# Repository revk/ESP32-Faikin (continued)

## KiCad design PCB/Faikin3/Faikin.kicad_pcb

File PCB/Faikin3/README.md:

# PCB

These files are for use in [KiCad](https://www.kicad.org) so can be edited as needed.

You should, technically, remove the A&A and AJK logos as they are trademark. If you are using for yourself, then fine, but you must not trade (i.e. sell boards you make) with these logos.

## Ordering

There are also `production` files for [JLCPCB](https://jlcpcb.com)

When ordering, you need the `gerber.zip`, `bom.csv`, and `position.csv` files.

### PCB

- Different Design: 2
- PCB Thickness: 1.0
- PCB Color: Black

### Assembly

- PCBA Type: Standard
- Assembly Side: Both Sides
- Tooling holes: Added by Customer

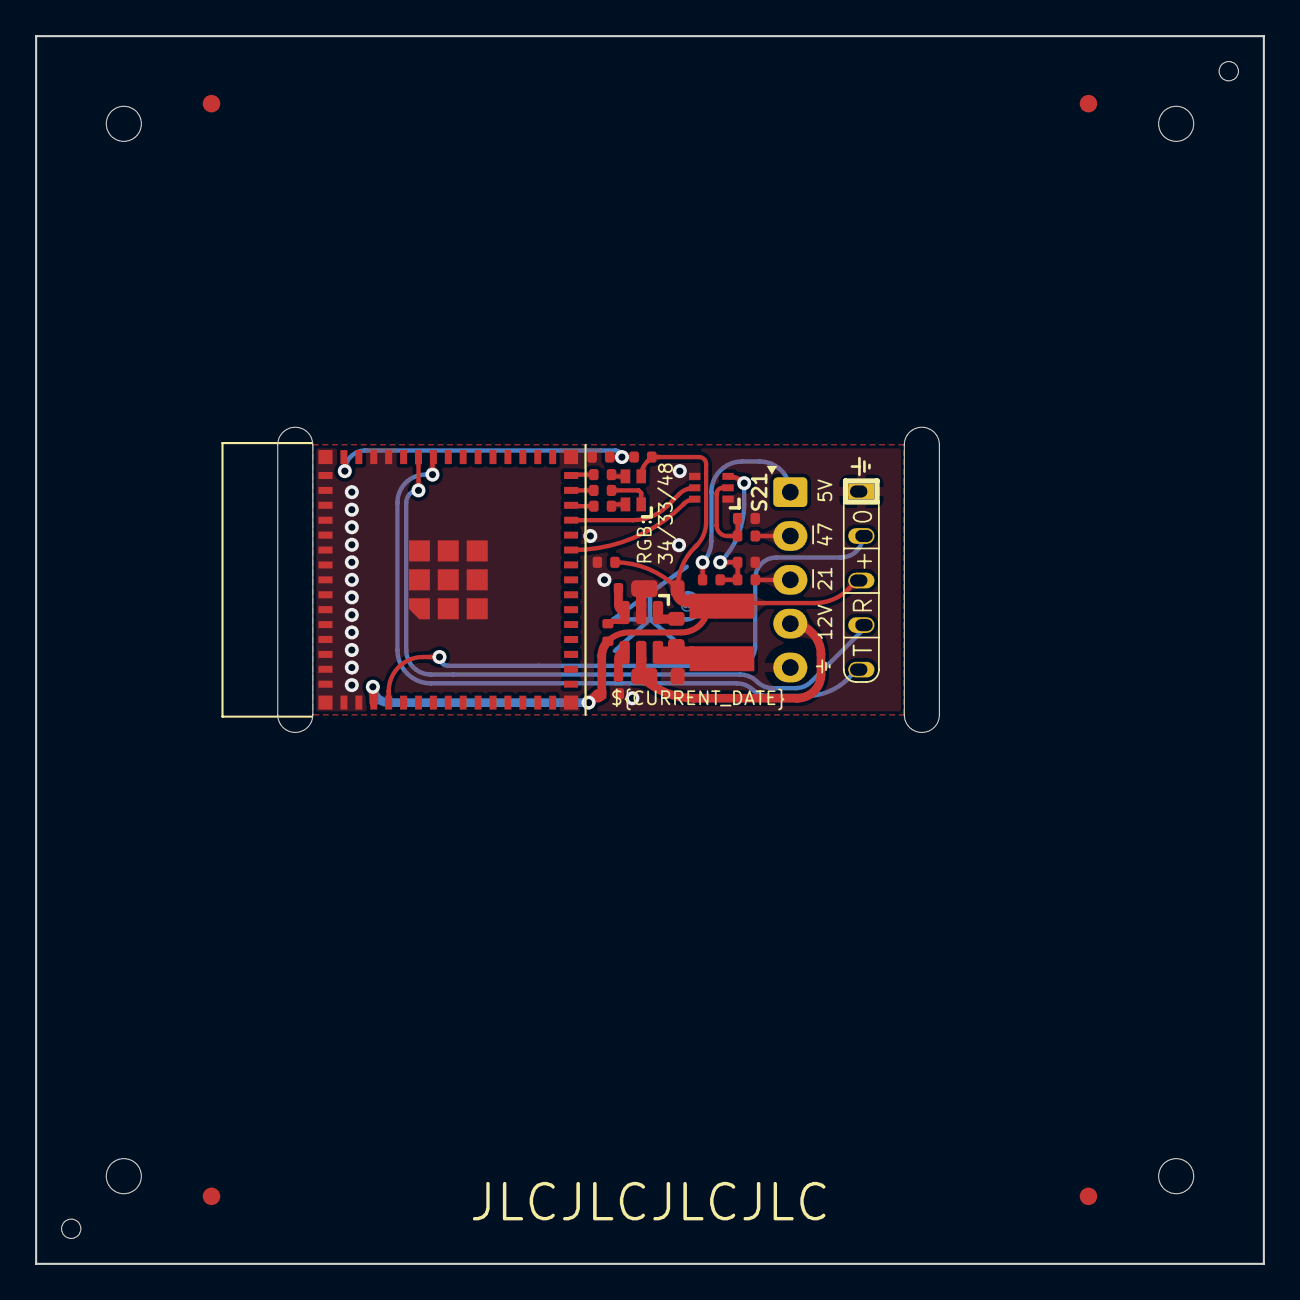
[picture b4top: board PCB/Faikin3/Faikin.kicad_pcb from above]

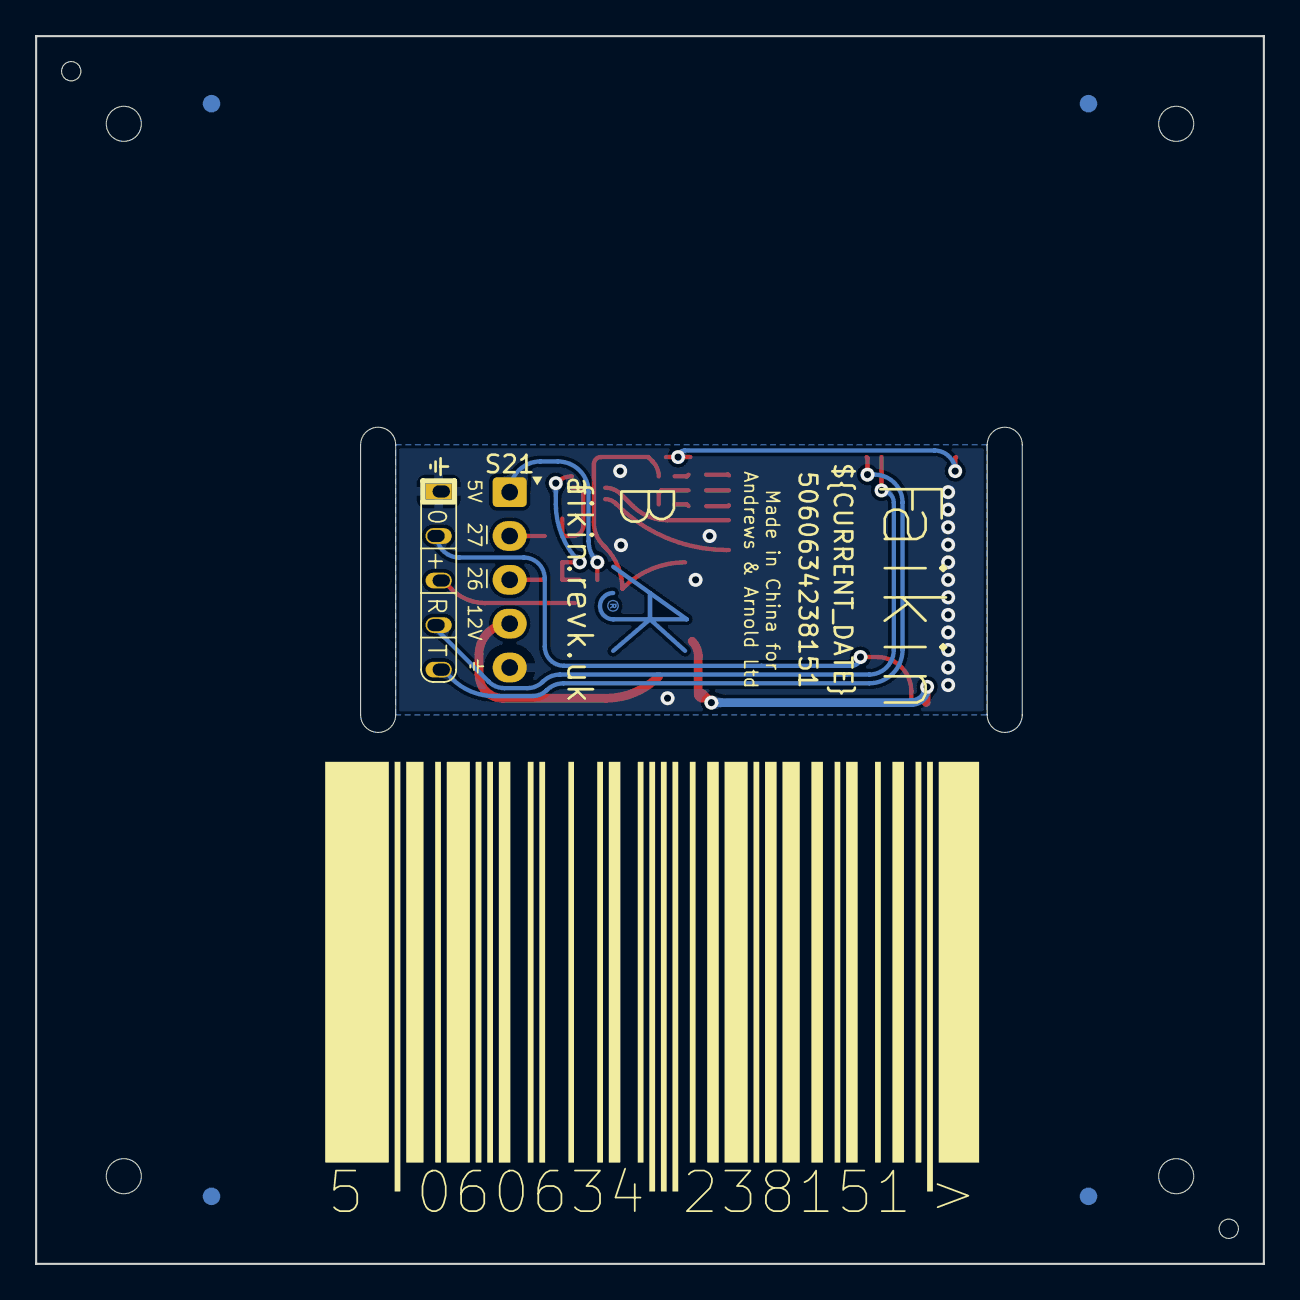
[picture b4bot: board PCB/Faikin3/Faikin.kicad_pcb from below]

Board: 2 copper layers, 70.0 x 70.0 mm, 30 parts (3 on the bottom side), 20 nets.

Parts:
C2: 100nF; C_0402
C3, C4: 33pF; C_0402
C5: 22uF; C_0402
C6: 1uF; C_0402
C8: 10uF 50V; C_0603_
C9: 10uF 6.3V; C_0603_
C10: 100nF; C_0603_
D2: RGB; LED-RGB-1.6x1.6
J1: 1x5; JST_EH_S5B-EH_1x05_P2.50mm_Horizontal
J3: Shelly
L2: 10uH; L_4x4_
Logo1: AJK
PCB1: 70x70; PCB7070
Q1: BSS138PS; SOT-363_SC-70-6
R1: 10k; R_0402
R2, R8: 100R; R_0402
R3: 10K; R_0402
R5: 680R; R_0402
R6: 2K; R_0402
R9: 124k; R_0402_
R10: 39k2; R_0402_
R11: 1M; R_0402_
R12: 220R; R_0402
U2: Barcode; EAN-5060634238151
U3: MD8942; SOT-23-6-MD8942
U4: ESP32-S3-MINI-1
V1, V2: VCUT70

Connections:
+3.3V: C2.1, C5.1, D2.4 (A), J3.3 (3V3), R3.1, U3.8 (VOUT), U4.3 (3V3)
B: R12.2, U4.30 (GPIO48)
DC: J1.4, U3.5 (VIN)
G: R6.2, U4.28 (GPIO33)
GND: C2.2, C3.1, C4.1, C5.2, C6.2, J1.5, J3.1 (GND), Q1.1 (SN), Q1.4 (DP), U3.2 (GND), U3.7 (GND), U4.1 (GND), U4.2 (GND), U4.42 (GND), U4.43 (GND), U4.46 (GND), U4.47 (GND), U4.48 (GND), U4.49 (GND), U4.50 (GND), U4.51 (GND), U4.52 (GND), U4.53 (GND), U4.54 (GND), U4.55 (GND), U4.56 (GND), U4.57 (GND), U4.58 (GND), U4.59 (GND), U4.60 (GND), U4.61 (GND), U4.62 (GND), U4.63 (GND), U4.64 (GND), U4.65 (GND)
unnamed: D2.3 (BK), R12.1
unnamed: D2.2 (GK), R6.1
unnamed: D2.1 (RK), R5.1
unnamed: J1.1, R1.1
unnamed: J1.2, R8.2
unnamed: J1.3, R2.2
unnamed: J3.2 (0), U4.4 (GPIO0)
unnamed: J3.4 (Rx), U4.40 (GPIO44)
unnamed: J3.5 (Tx), U4.39 (GPIO43)
unnamed: C4.2, Q1.2 (GN), R8.1
unnamed: C3.2, Q1.3 (SP), R1.2, R2.1
unnamed: C6.1, R3.2, U4.45 (EN)
R: R5.2, U4.29 (GPIO34)
RX: Q1.6 (DN), U4.25 (GPIO21)
TX: Q1.5 (GP), U4.27 (GPIO47)

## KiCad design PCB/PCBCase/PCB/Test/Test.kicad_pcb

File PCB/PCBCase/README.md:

* PCB Case

This is designed to take an KICad 6 kicad_pcb file and produce an openscad file that is the case.
The problem is that you need 3D models for your parts for this to work sensibly, so the C code has a list of footprints as basic openscad outlines. This is not like the 3D models in KiCad which are accurate, it is simply boxes and shapes that allow for the 3D box to have a sensibly sized cut out for the part.
In many cases this means the model is just a cuboid. But in some cases it is slightly more important as it has the attached connector included.
Any parts of the design that would breach the case cause cut outs and supports in the case surround.

## models

Modules are individual scad instructions, and can be named as the first match of :-

- The footprint name (without `prefix:`)
- The footprint name (without `prefix:`) where single numeric component is replaced with `0`
- The 3D model name(s) in the footprint

The module is called with `pushed` and `hulled` which are Boolean, and in the case of the `0` version, with `n` which is the number that was replaced with 0.

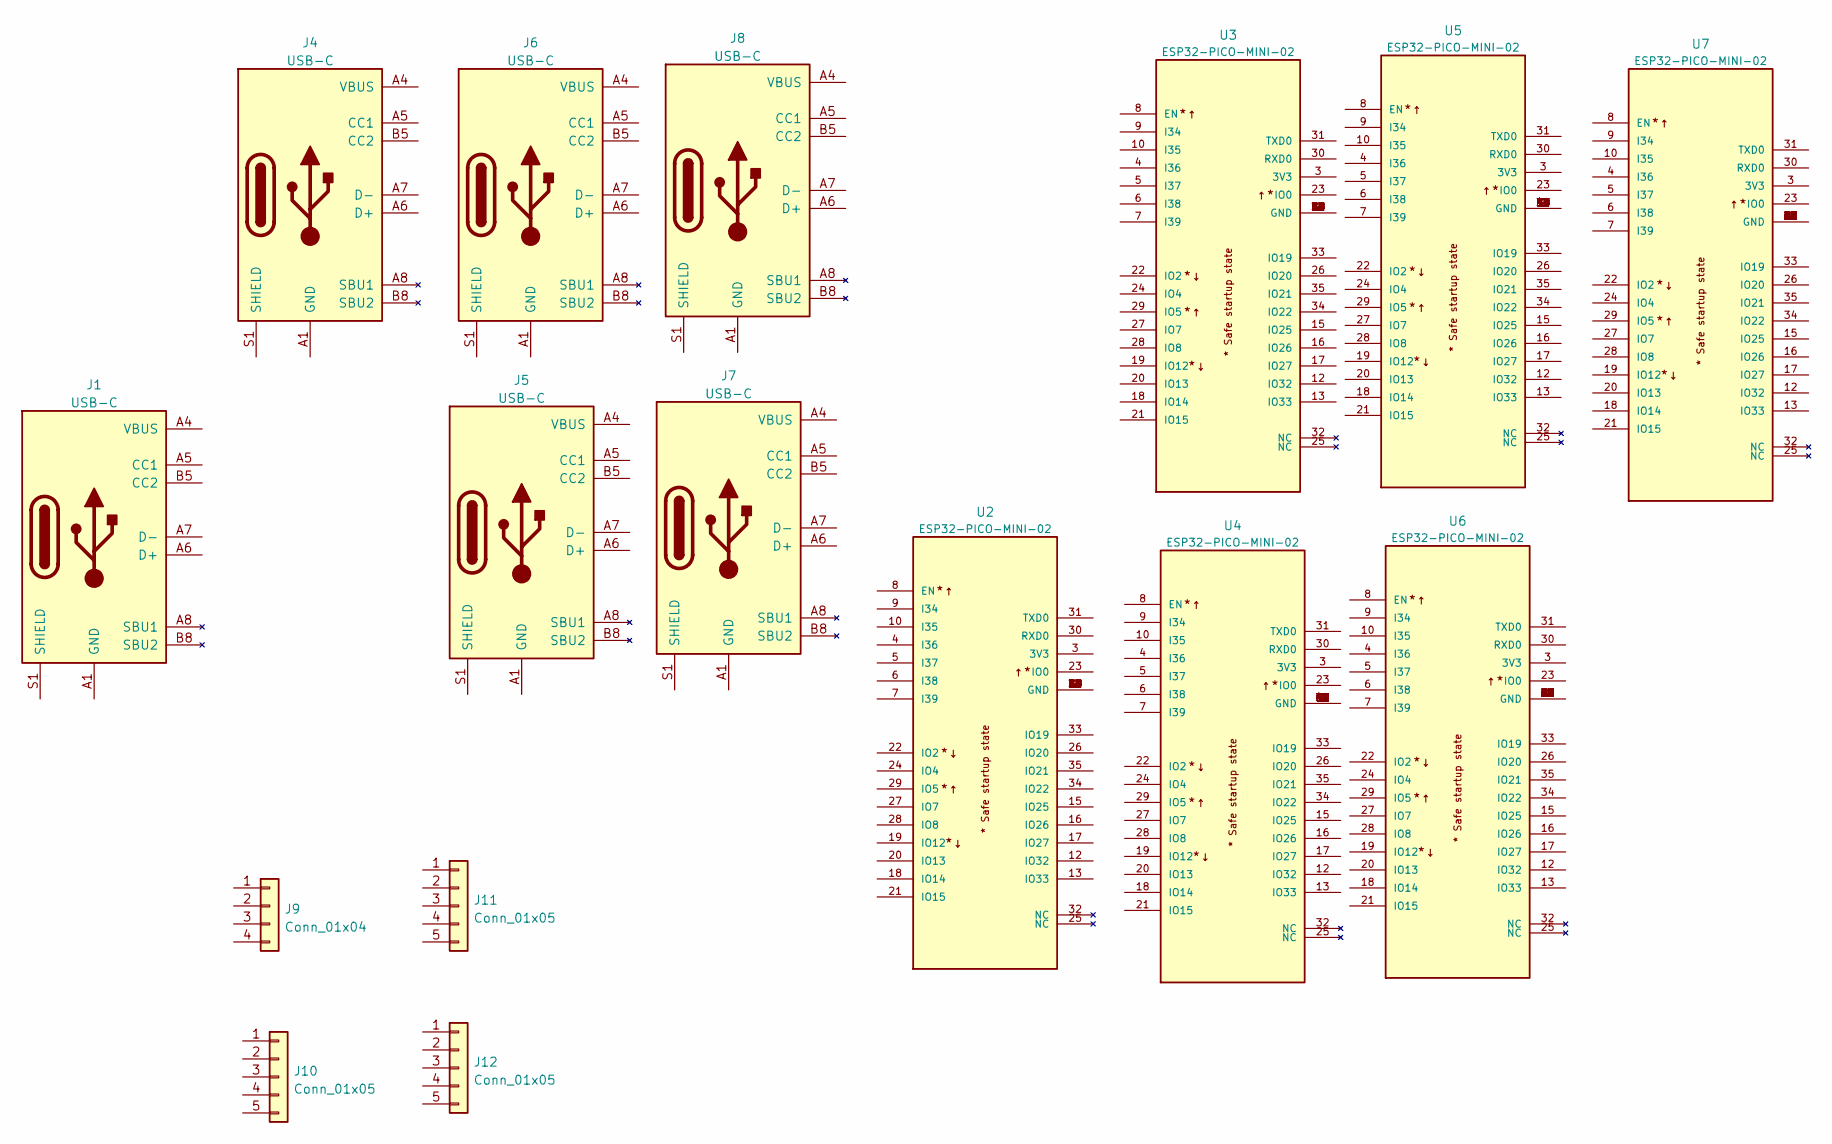
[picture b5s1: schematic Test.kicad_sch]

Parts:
J1, J4, J5, J6, J7, J8: USB-C; USC16-TR-Round
J9: Conn_01x04; JLC-PinHeader_1x04_P2.54mm_Right
J10: Conn_01x05; PTSM-HH-5-RA-P
J11: Conn_01x05; PTSM-HH-5-RA
J12: Conn_01x05; PTSM-HH-5-RA-P-SMD
U2, U3, U4, U5, U6, U7: ESP32-PICO-MINI-02; PARTREV v1.0

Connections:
unnamed: J1.A1 (GND), J1.A12 (GND), J1.B1 (GND), J1.B12 (GND)
unnamed: J1.A4 (VBUS), J1.A9 (VBUS), J1.B4 (VBUS), J1.B9 (VBUS)
unnamed: J1.A6 (D+), J1.B6 (D+)
unnamed: J1.A7 (D-), J1.B7 (D-)
unnamed: J4.A1 (GND), J4.A12 (GND), J4.B1 (GND), J4.B12 (GND)
unnamed: J4.A4 (VBUS), J4.A9 (VBUS), J4.B4 (VBUS), J4.B9 (VBUS)
unnamed: J4.A6 (D+), J4.B6 (D+)
unnamed: J4.A7 (D-), J4.B7 (D-)
unnamed: J5.A1 (GND), J5.A12 (GND), J5.B1 (GND), J5.B12 (GND)
unnamed: J5.A4 (VBUS), J5.A9 (VBUS), J5.B4 (VBUS), J5.B9 (VBUS)
unnamed: J5.A6 (D+), J5.B6 (D+)
unnamed: J5.A7 (D-), J5.B7 (D-)
unnamed: J6.A1 (GND), J6.A12 (GND), J6.B1 (GND), J6.B12 (GND)
unnamed: J6.A4 (VBUS), J6.A9 (VBUS), J6.B4 (VBUS), J6.B9 (VBUS)
unnamed: J6.A6 (D+), J6.B6 (D+)
unnamed: J6.A7 (D-), J6.B7 (D-)
unnamed: J7.A1 (GND), J7.A12 (GND), J7.B1 (GND), J7.B12 (GND)
unnamed: J7.A4 (VBUS), J7.A9 (VBUS), J7.B4 (VBUS), J7.B9 (VBUS)
unnamed: J7.A6 (D+), J7.B6 (D+)
unnamed: J7.A7 (D-), J7.B7 (D-)
unnamed: J8.A1 (GND), J8.A12 (GND), J8.B1 (GND), J8.B12 (GND)
unnamed: J8.A4 (VBUS), J8.A9 (VBUS), J8.B4 (VBUS), J8.B9 (VBUS)
unnamed: J8.A6 (D+), J8.B6 (D+)
unnamed: J8.A7 (D-), J8.B7 (D-)
unnamed: U2.1 (GND), U2.2 (GND), U2.11 (GND), U2.14 (GND), U2.36 (GND), U2.37 (GND), U2.38 (GND), U2.39 (GND), U2.40 (GND), U2.41 (GND), U2.42 (GND), U2.43 (GND), U2.44 (GND), U2.45 (GND), U2.46 (GND), U2.47 (GND), U2.48 (GND), U2.49 (GND), U2.50 (GND), U2.51 (GND), U2.52 (GND), U2.53 (GND)
unnamed: U3.1 (GND), U3.2 (GND), U3.11 (GND), U3.14 (GND), U3.36 (GND), U3.37 (GND), U3.38 (GND), U3.39 (GND), U3.40 (GND), U3.41 (GND), U3.42 (GND), U3.43 (GND), U3.44 (GND), U3.45 (GND), U3.46 (GND), U3.47 (GND), U3.48 (GND), U3.49 (GND), U3.50 (GND), U3.51 (GND), U3.52 (GND), U3.53 (GND)
unnamed: U4.1 (GND), U4.2 (GND), U4.11 (GND), U4.14 (GND), U4.36 (GND), U4.37 (GND), U4.38 (GND), U4.39 (GND), U4.40 (GND), U4.41 (GND), U4.42 (GND), U4.43 (GND), U4.44 (GND), U4.45 (GND), U4.46 (GND), U4.47 (GND), U4.48 (GND), U4.49 (GND), U4.50 (GND), U4.51 (GND), U4.52 (GND), U4.53 (GND)
unnamed: U5.1 (GND), U5.2 (GND), U5.11 (GND), U5.14 (GND), U5.36 (GND), U5.37 (GND), U5.38 (GND), U5.39 (GND), U5.40 (GND), U5.41 (GND), U5.42 (GND), U5.43 (GND), U5.44 (GND), U5.45 (GND), U5.46 (GND), U5.47 (GND), U5.48 (GND), U5.49 (GND), U5.50 (GND), U5.51 (GND), U5.52 (GND), U5.53 (GND)
unnamed: U6.1 (GND), U6.2 (GND), U6.11 (GND), U6.14 (GND), U6.36 (GND), U6.37 (GND), U6.38 (GND), U6.39 (GND), U6.40 (GND), U6.41 (GND), U6.42 (GND), U6.43 (GND), U6.44 (GND), U6.45 (GND), U6.46 (GND), U6.47 (GND), U6.48 (GND), U6.49 (GND), U6.50 (GND), U6.51 (GND), U6.52 (GND), U6.53 (GND)
unnamed: U7.1 (GND), U7.2 (GND), U7.11 (GND), U7.14 (GND), U7.36 (GND), U7.37 (GND), U7.38 (GND), U7.39 (GND), U7.40 (GND), U7.41 (GND), U7.42 (GND), U7.43 (GND), U7.44 (GND), U7.45 (GND), U7.46 (GND), U7.47 (GND), U7.48 (GND), U7.49 (GND), U7.50 (GND), U7.51 (GND), U7.52 (GND), U7.53 (GND)

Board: 2 copper layers, 16 parts (6 on the bottom side), 30 nets, no tracks yet.

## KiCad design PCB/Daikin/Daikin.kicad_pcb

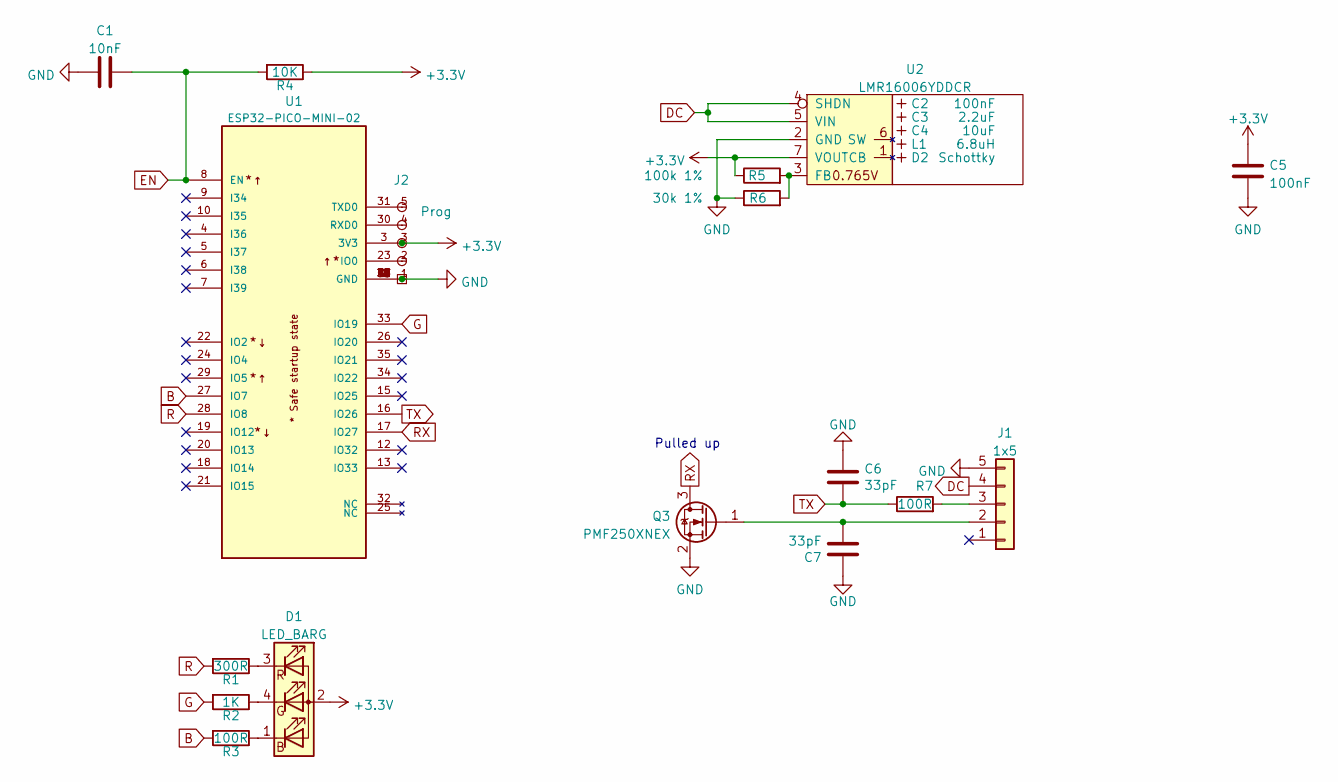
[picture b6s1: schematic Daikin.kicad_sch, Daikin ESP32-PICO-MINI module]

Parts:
C1: 10nF; C_0603; Part No 0603-10nF-50V
C2: 100nF; C_0603_; LCSC Part # C30926
C3: 2.2uF; C_0805_; LCSC Part # C19110
C4: 10uF; C_0805_; LCSC Part # C17024
C5: 100nF; C_0603; Part No 0603-100nF-25V
C6, C7: 33pF; C_0603; Part No 0603-33pF-50V
D1: LED_BARG; MHS190RGBCT; LCSC Part # C409798
D2: Schottky; D_1206_; LCSC Part # C143805
J1: 1x5; JST_EH_S5B-EH_1x05_P2.50mm_Horizontal; LCSC Part # C225427
J2: Prog; Shelly
L1: 6.8uH; L_4x4_; LCSC Part # C354575
Q3: PMF250XNEX; SOT-323_SC-70; Part No PMF250XNEX; LCSC Part # C504047
R1: 300R; R_0603; Part No 0603-680R
R2: 1K; R_0603; Part No 0603-2K
R3: 100R; R_0603; Part No 0603-220R
R4: 10K; R_0603; Part No 0603-10K
R5: 100k 1%; R_0603; LCSC Part # C14675
R6: 30k 1%; R_0603; LCSC Part # C100001
R7: 100R; R_0603; LCSC Part # C105588
U1: ESP32-PICO-MINI-02; PARTREV v1.0; LCSC Part # C2980306
U2: LMR16006YDDCR; SOT-23-Thin-6-Reg; Part No LMR16006YDDCR; LCSC Part # C290195

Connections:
+3.3V: C5.1, D1.2 (A), J2.3 (3V3), R4.1, R5.1, U1.3 (3V3), U2.7 (VOUT)
B: R3.2, U1.27 (IO7)
DC: J1.4, U2.4 (SHDN), U2.5 (VIN)
EN: C1.2, R4.2, U1.8 (EN)
G: R2.2, U1.33 (IO19)
GND: C1.1, C5.2, C6.1, C7.1, J1.5, J2.1 (GND), Q3.2 (S), R6.1, U1.1 (GND), U1.2 (GND), U1.11 (GND), U1.14 (GND), U1.36 (GND), U1.37 (GND), U1.38 (GND), U1.39 (GND), U1.40 (GND), U1.41 (GND), U1.42 (GND), U1.43 (GND), U1.44 (GND), U1.45 (GND), U1.46 (GND), U1.47 (GND), U1.48 (GND), U1.49 (GND), U1.50 (GND), U1.51 (GND), U1.52 (GND), U1.53 (GND), U2.2 (GND)
unnamed: C7.2, J1.2, Q3.1 (G)
unnamed: D1.1 (BK), R3.1
unnamed: D1.3 (RK), R1.1
unnamed: D1.4 (GK), R2.1
unnamed: J1.3, R7.2
unnamed: J2.2 (0), U1.23 (IO0)
unnamed: J2.4 (Rx), U1.30 (RXD0)
unnamed: J2.5 (Tx), U1.31 (TXD0)
unnamed: R5.2, R6.2, U2.3 (FB)
R: R1.2, U1.28 (IO8)
RX: Q3.3 (D), U1.17 (IO27)
TX: C6.2, R7.1, U1.16 (IO26)

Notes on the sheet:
Pulled up

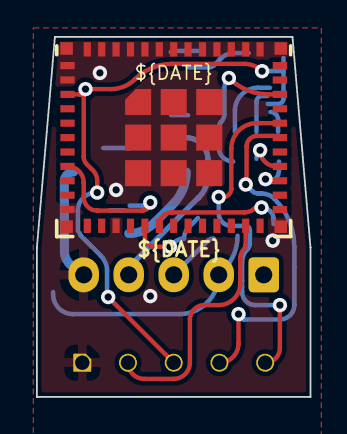
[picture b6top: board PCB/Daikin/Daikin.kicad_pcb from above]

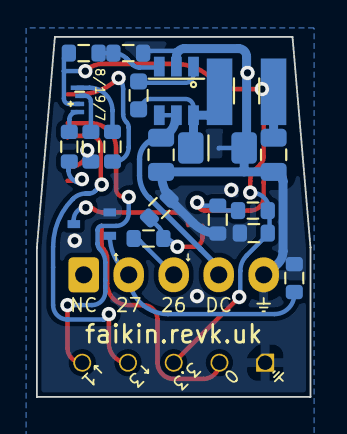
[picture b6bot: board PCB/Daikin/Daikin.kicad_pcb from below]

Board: 2 copper layers, 15.2 x 20.0 mm, 22 parts (20 on the bottom side), 18 nets.

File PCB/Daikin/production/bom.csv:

Designator,Footprint,Quantity,Value,LCSC Part #
C1,C_0603,1,10nF,
C2,C_0603_,1,100nF,C30926
C3,C_0805_,1,2.2uF,C19110
C4,C_0805_,1,10uF,C17024
C5,C_0603,1,100nF,
"C6, C7",C_0603,2,33pF,
D1,MHS190RGBCT,1,LED_BARG,C409798
D2,D_1206_,1,Schottky,C143805
J1,PinHeader_1x05_P2.54mm_Right,1,1x5,C225491
L1,L_4x4_,1,6.8uH,C354575
Q3,SOT-323_SC-70,1,PMF250XNEX,C504047
R1,R_0603,1,300R,
R2,R_0603,1,1K,
"R3, R7",R_0603,2,100R,
R4,R_0603,1,10K,
R5,R_0603,1,100k 1%,C14675
R6,R_0603,1,30k 1%,C100001
U1,ESP32-PICO-MINI-02,1,ESP32-PICO-MINI-02,C2980306
U2,SOT-23-Thin-6-Reg,1,LMR16006YDDCR,C290195

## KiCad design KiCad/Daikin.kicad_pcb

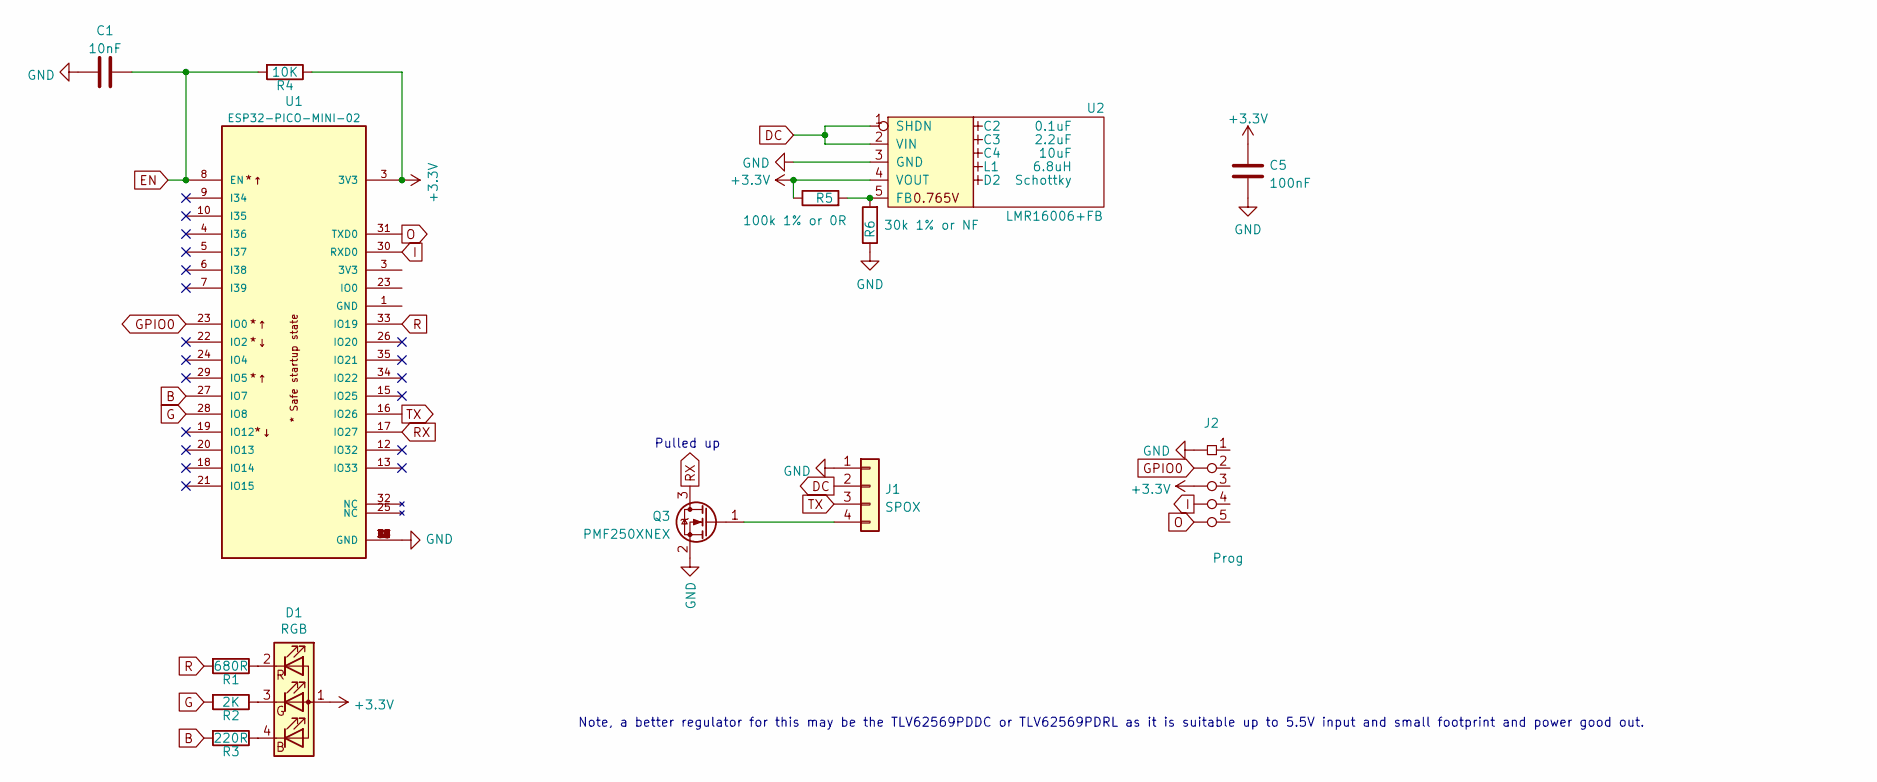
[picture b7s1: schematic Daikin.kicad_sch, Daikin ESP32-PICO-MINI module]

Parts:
C1: 10nF; C_0603; Part No 0603-10nF-50V
C2: 0.1uF; C_0603_; Part No 0603-100nF-50V
C3: 2.2uF; C_0805_; Part No 0805-2.2uF-25V
C4: 10uF; C_0805_; Part No 0805-10uF-16V
C5: 100nF; C_0603; Part No 0603-100nF-25V
D1: RGB; LED-RGB-1.6x1.6; Part No APTF1616LSEEZGKQBKC
D2: Schottky; D_1206_; Part No CD1206-B2100
J1: SPOX; Molex_MiniSPOX_H4RA; Part No 22057025
J2: Prog; Shelly
L1: 6.8uH; L_4x4_; Part No TYA40206R8M-10
Q3: PMF250XNEX; SOT-323_SC-70; Part No PMF250XNEX
R1: 680R; R_0603; Part No 0603-680R
R2: 2K; R_0603; Part No 0603-2K
R3: 220R; R_0603; Part No 0603-220R
R4: 10K; R_0603; Part No 0603-10K
R5: 100k 1% or 0R; R_0603; Part No 0603-100k
R6: 30k 1% or NF; R_0603; Part No 0603-30k
U1: ESP32-PICO-MINI-02; PARTREV v1.0
U2: LMR16006+FB; SOT-23-Thin-6-Reg; Part No LMR16006YQ3

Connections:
+3V3: C5.1, D1.1 (A), J2.3 (3V3), R4.1, R5.1, U1.3 (3V3), U2.4 (VOUT)
B: R3.2, U1.27 (IO7)
DC: J1.2, U2.1 (SHDN), U2.2 (VIN)
EN: C1.2, R4.2, U1.8 (EN)
G: R2.2, U1.28 (IO8)
GND: C1.1, C5.2, J1.1, J2.1 (GND), Q3.2 (S), R6.1, U1.1 (GND), U1.2 (GND), U1.11 (GND), U1.14 (GND), U1.36 (GND), U1.37 (GND), U1.38 (GND), U1.39 (GND), U1.40 (GND), U1.41 (GND), U1.42 (GND), U1.43 (GND), U1.44 (GND), U1.45 (GND), U1.46 (GND), U1.47 (GND), U1.48 (GND), U1.49 (GND), U1.50 (GND), U1.51 (GND), U1.52 (GND), U1.53 (GND), U2.3 (GND)
GPIO0: J2.2 (0), U1.23 (IO0)
I: J2.4 (Rx), U1.30 (RXD0)
unnamed: D1.2 (RK), R1.1
unnamed: D1.3 (GK), R2.1
unnamed: D1.4 (BK), R3.1
unnamed: J1.4, Q3.1 (G)
unnamed: R5.2, R6.2, U2.5 (FB)
O: J2.5 (Tx), U1.31 (TXD0)
R: R1.2, U1.33 (IO19)
RX: Q3.3 (D), U1.17 (IO27)
TX: J1.3, U1.16 (IO26)

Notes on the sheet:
Pulled up
Note, a better regulator for this may be the TLV62569PDDC or TLV62569PDRL as it is suitable up to 5.5V input and small footprint and power good out.

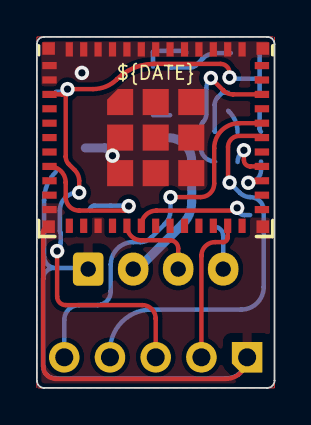
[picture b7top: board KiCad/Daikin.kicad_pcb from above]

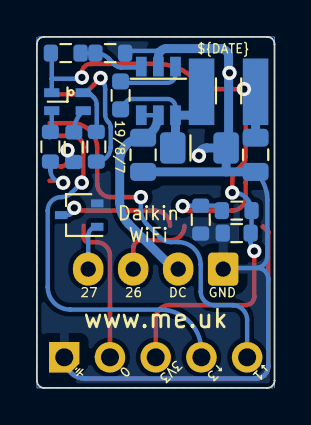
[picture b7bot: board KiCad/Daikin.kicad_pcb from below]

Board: 2 copper layers, 13.2 x 19.5 mm, 19 parts (17 on the bottom side), 17 nets.

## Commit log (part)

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2025-04-14 Beta
2025-04-19 Library update
2025-04-30 Started on Faikin remote
2025-04-30 Tidy
2025-05-01 Faikin remore work
2025-05-03 Faikin power control fixes
2025-05-03 Flag bad mode
2025-05-04 Tweak
2025-05-05 Release
2025-05-09 Handle swing V with no swing H, and change name from `noswingw` to `noswingv`, what was it `w`?!
2025-05-09 Added noecono
2025-05-09 latest library
2025-05-13 Additional BLE options
2025-05-13 Tweak BLE
2025-05-13 BLE picks up names better
2025-05-13 Match MAC for BLE and name
2025-05-23 Render update
2025-05-28 More logging
2025-05-28 Skip extra rx packets
2025-05-28 Retry listen for reply in S21
2025-05-28 RG poll faster
2025-06-02 Handle unexpected fan levels from faikin remote
2025-06-07 `autotopic` and `autopayload`
2025-06-14 Help
2025-06-14 fanmode instead of fanstep
2025-06-19 Loopback
2025-06-19 Start startup AT logic
2025-06-21 LED start sequence
2025-06-21 Update website
2025-06-25 Only issuing S3 code now
2025-06-25 Update README.md (video)
2025-07-04 Dev for 2AS supply
2025-07-04 Render new dev board
2025-07-05 Tweaks
2025-07-06 Yweak
2025-07-09 no.flap
2025-07-09 Latest render
2025-07-18 feat: strip inline styling to separate webapp.css file and update gitignore
2025-07-18 fix: remove unnecessary comment and ensure proper file termination
2025-07-20 Moved caps away from heat
2025-07-20 Ordering new batch
2025-07-21 PCB tweak
2025-07-22 Pico added
2025-07-24 Tweak caps and inductor
2025-07-24 You can never have too many caps.
2025-07-31 New PCB
2025-08-01 Case update
2025-08-02 Layout
2025-08-02 Latest tracking
2025-08-04 New 0201 footprint
2025-08-04 Updated 3D
2025-08-05 Thicker
2025-08-05 Tweak case
2025-08-08 Revised test points
2025-08-09 Case tidy
2025-08-11 New case
2025-08-11 Adjust
2025-08-11 Fit adjust
2025-08-11 case tweaks
2025-08-12 Case tweak
2025-08-12 Re-render cases
2025-08-12 Separate STL files
2025-08-12 Simpler
2025-08-12 Tweak case lip
2025-08-12 Yet further revised case design
2025-08-12 More tweaks
2025-08-13 Track adjust
2025-08-13 Tweak layout, and more test points
2025-08-15 Separate debug and s21extra logic
2025-08-16 more nak
2025-08-17 Re render
2025-08-17 Fiducials
2025-08-18 New cases
2025-08-20 Slight change to case parameters
2025-08-22 Revert
2025-08-22 Thicker top
2025-08-23 Higher inductor
2025-08-24 Date code
2025-08-25 Tidy readme
2025-08-26 Default hourly poll disabled as clicks/beeps
2025-08-26 Latest PCB
2025-08-26 Models for case
2025-08-26 BOM tweak
2025-08-27 Back to ENIG finish for renders
2025-09-08 Render (but wrong colour?)
2025-09-14 TC2030 on top
2025-09-15 CGAL for now
2025-09-21 Allow settings for unknown fields whilst starting up.
2025-09-24 Rerender
2025-09-26 New URL/links
2025-09-27 Disable flash button
2025-09-28 Rework with new LED and TC2030 rotate
2025-09-29 Handle A/M/V message responses
2025-09-30 Allow short M/V messages
2025-09-30 Filenames
2025-10-01 Case render
2025-10-01 Re-render
2025-10-01 Try that
2025-10-03 ATE work
2025-10-03 Beta for factory flash
2025-10-03 Issue for factory
2025-10-05 ATE tweak
2025-10-05 ATE fix
2025-10-06 Lib update
2025-10-06 Tweak margins
2025-10-07 Minor tweaks
2025-10-07 rsync to new ota server
2025-10-07 Odd one
2025-10-10 New LEDs
2025-10-12 LED 3D update
2025-10-14 Update Setup.md (Typo fixes)
    Fix a few minor typos
2025-10-26 New renders (faster)
2025-10-30 Missing files
2025-10-30 Wrong files
2025-10-30 Logo
2025-10-30 Wording
2025-11-01 Update legacy URL for steamer and other values
2025-11-05 General render and README updates
2025-11-05 Even neater
2025-11-05 Even cleaner render
2025-11-05 Render LED
2025-11-11 New ota dir
2025-11-11 Fix NVS settings partition name
2025-11-12 Name change (first edit)
2025-11-12 Rename to Faikout (first edit)
2025-11-12 Rename
2025-11-12 New name
2025-11-12 name change work
2025-11-12 Name chaneg
2025-11-12 factorygpio
2025-11-12 amazon link
2025-11-14 More name change stuff
2025-11-14 Table keys fix
2025-11-15 Summary MQTT includes humidity (`hum`) which is from BLE sensor
